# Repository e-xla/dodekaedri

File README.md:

# dodekaedri
dodekaedrin muotoinen radio ":D" /  dodecahedron shaped radio ":D"

------
This project aims to create truly affordable (<50€) 40m SSB QRP HAM radio kit.
Intention is to create such easy-approach kit that enables new (and old) HAMs to learn about radios, electronics and so on.

Some intended specs include:
* included SWR-meter
* ~5-10W of raw electromagnetic power
* graphical UI
* 2 mixer stages, one physical, one done with software

(Antenna not included)

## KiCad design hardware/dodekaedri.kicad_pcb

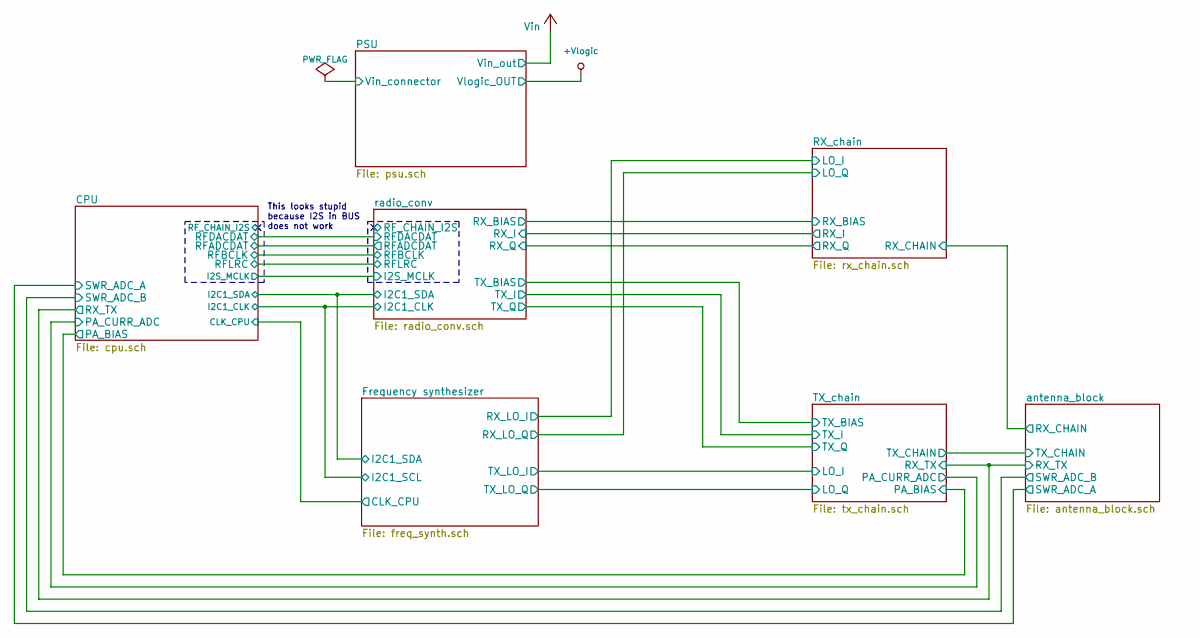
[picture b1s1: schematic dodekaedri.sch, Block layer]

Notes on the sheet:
This looks stupid because I2S in BUS does not work

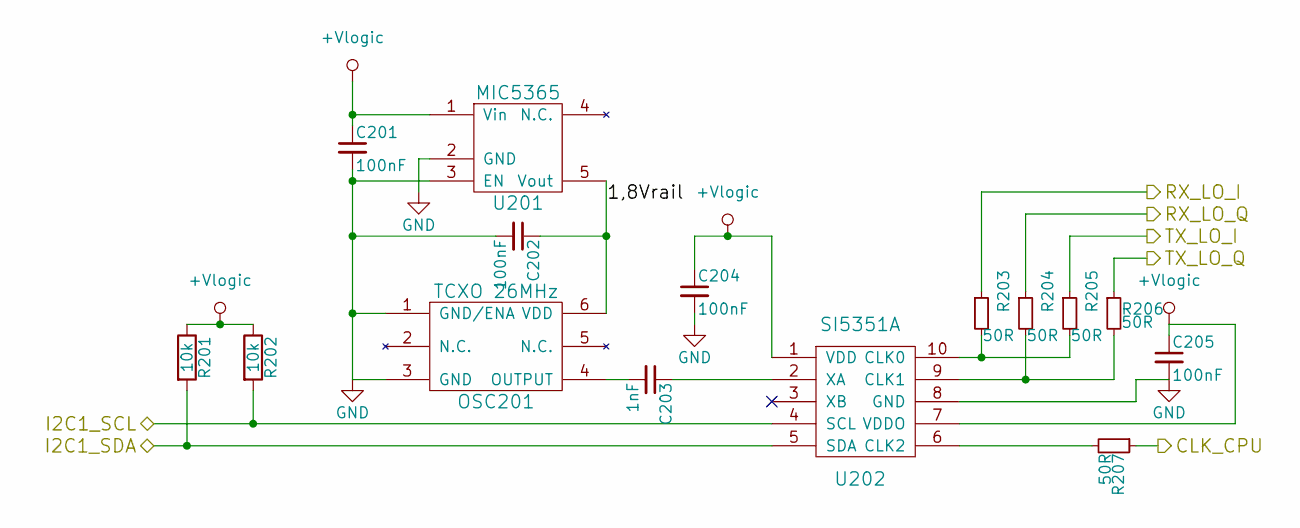
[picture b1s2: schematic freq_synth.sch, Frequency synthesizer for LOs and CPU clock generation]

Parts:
C201, C202, C204, C205: 100nF; C_0805
C203: 1nF; C_0805
OSC201: TCXO 26MHz
R201, R202: 10k; R_0805_HandSoldering
R203, R204, R205, R206, R207: 50R; R_0805_HandSoldering
U201: MIC5365
U202: SI5351A

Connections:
/CPU/CLK_CPU: R207.1; also elsewhere on the board
/CPU/I2C1_CLK: R202.2, U202.4 (SCL); also elsewhere on the board
/CPU/I2C1_SDA: R201.2, U202.5 (SDA); also elsewhere on the board
/Frequency synthesizer/1,8Vrail: C202.1, OSC201.6 (VDD), U201.5 (Vout)
/RX_chain/LO_I: R203.1; also elsewhere on the board
/RX_chain/LO_Q: R204.1; also elsewhere on the board
/TX_chain/LO_I: R205.1; also elsewhere on the board
/TX_chain/LO_Q: R206.1; also elsewhere on the board
GND: C201.2, C202.2, C204.2, C205.2, OSC201.1 (GND/ENA), OSC201.3 (GND), U201.2 (GND), U201.3 (EN), U202.8 (GND); also elsewhere on the board
unnamed: C203.1, U202.2 (XA)
unnamed: C203.2, OSC201.4 (OUTPUT)
unnamed: R203.2, R205.2, U202.10 (CLK0)
unnamed: R204.2, R206.2, U202.9 (CLK1)
unnamed: R207.2, U202.6 (CLK2)

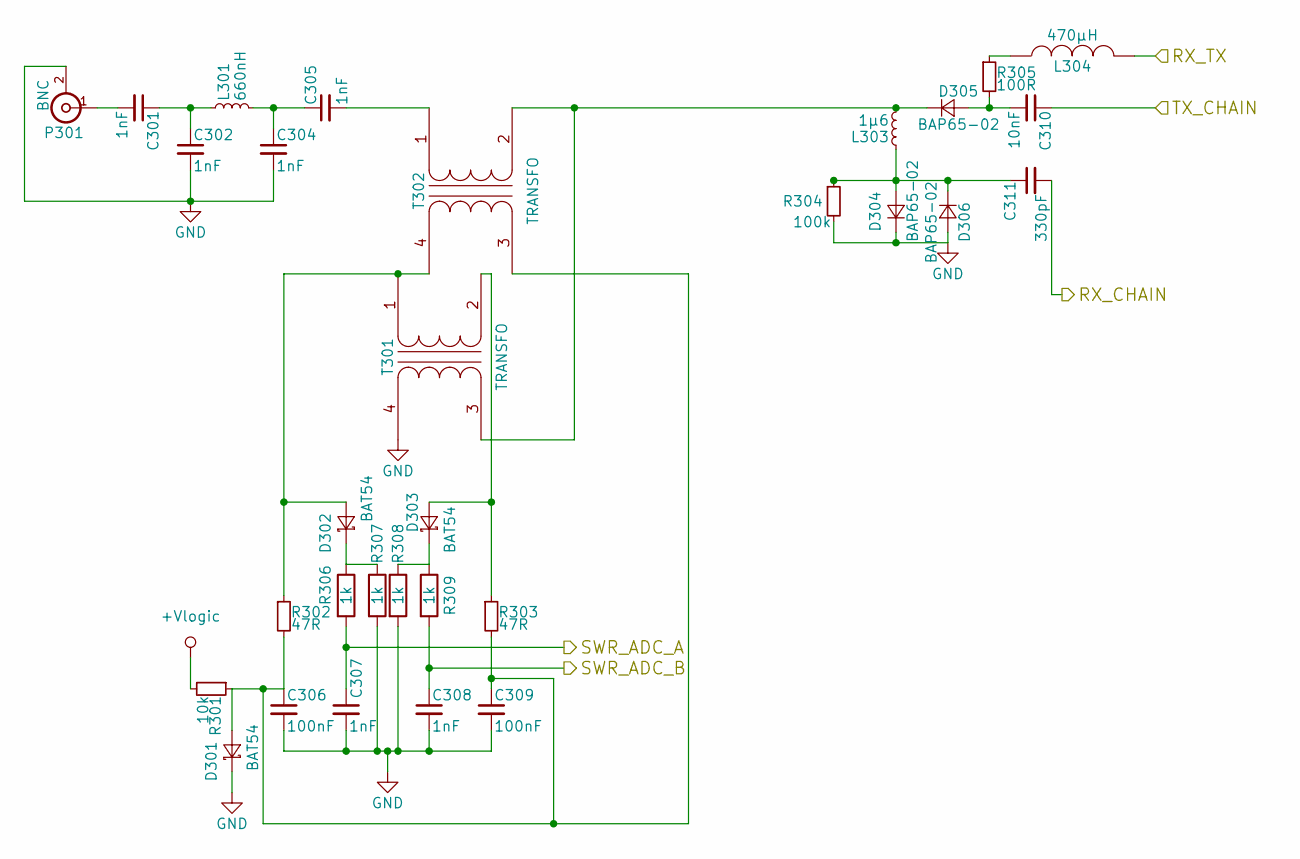
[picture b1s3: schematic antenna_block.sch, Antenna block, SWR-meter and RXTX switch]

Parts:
C301, C302, C304, C305, C307, C308: 1nF; C_0805_HandSoldering
C306, C309: 100nF; C_0805_HandSoldering
C310: 10nF; C_0805_HandSoldering
C311: 330pF; C_0805_HandSoldering
D301, D302, D303: BAT54; SOT-23_HS_2-1-3
D304, D305, D306: BAP65-02; SOD-523
L301: 660nH; Neosid_Air-Coil_SML_5turn_HDM0531A
L303: 1µ6; Neosid_Air-Coil_SML_5turn_HDM0531A
L304: 470µH; SMT_1007
P301: BNC; BNC_right_angle
R301: 10k; R_0805_HandSoldering
R302, R303: 47R; R_0805_HandSoldering
R304: 100k; R_0805_HandSoldering
R305: 100R; R_0805_HandSoldering
R306, R307, R308, R309: 1k; R_0805_HandSoldering
T301, T302: TRANSFO; TRANSF_pads

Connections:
/CPU/RX_TX: L304.2; also elsewhere on the board
/CPU/SWR_ADC_A: C307.1, R306.2; also elsewhere on the board
/CPU/SWR_ADC_B: C308.1, R309.2; also elsewhere on the board
/RX_chain/RX_CHAIN: C311.2; also elsewhere on the board
/TX_chain/TX_CHAIN: C310.1; also elsewhere on the board
GND: C302.2, C304.2, C306.2, C307.2, C308.2, C309.2, D301.1 (K), D304.1 (K), D306.2 (A), P301.2 (Ext), R304.2, R307.2, R308.2, T301.4 (SB); also elsewhere on the board
unnamed: C301.1, C302.1, L301.1
unnamed: C301.2, P301.1 (In)
unnamed: C304.1, C305.1, L301.2
unnamed: C305.2, T302.1 (AA)
unnamed: C306.1, C309.1, D301.2 (A), R301.1, R302.2, R303.2, T302.3 (SA)
unnamed: C310.2, D305.2 (A), R305.2
unnamed: C311.1, D304.2 (A), D306.1 (K), L303.1, R304.1
unnamed: D302.1 (K), R306.1, R307.1
unnamed: D302.2 (A), R302.1, T301.1 (AA), T302.4 (SB)
unnamed: D303.1 (K), R308.1, R309.1
unnamed: D303.2 (A), R303.1, T301.2 (AB)
unnamed: D305.1 (K), L303.2, T301.3 (SA), T302.2 (AB)
unnamed: L304.1, R305.1

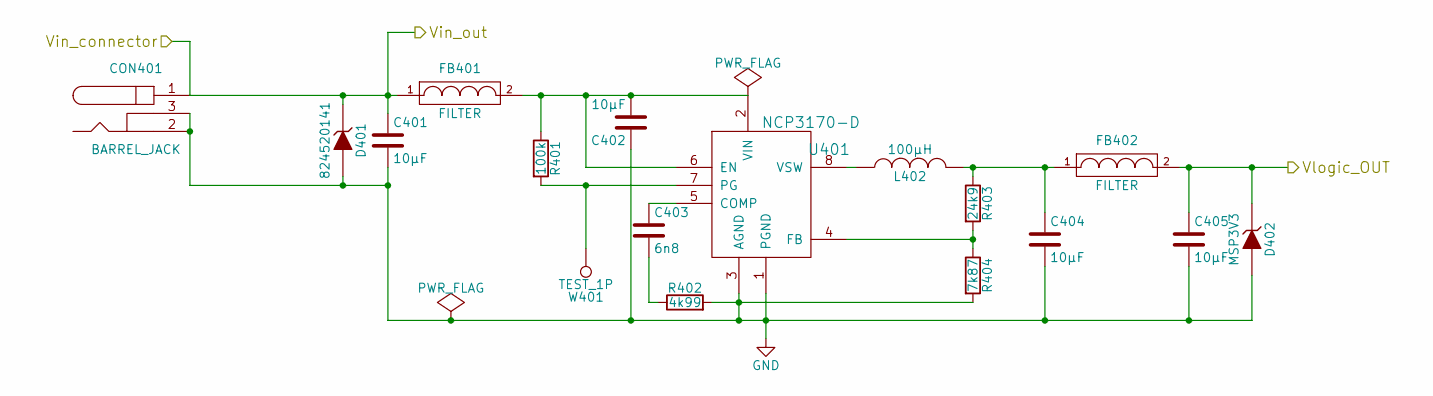
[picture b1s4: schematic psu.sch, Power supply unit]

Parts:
C401, C402, C404, C405: 10µF; C_0805_HandSoldering
C403: 6n8; C_0805_HandSoldering
CON401: BARREL_JACK
D401: 824520141; SMA_Handsoldering
D402: MSP3V3; Micro_SMP
FB401, FB402: FILTER; R_0805_HandSoldering
L402: 100µH; psu_ind
R401: 100k; R_0805_HandSoldering
R402: 4k99; R_0805_HandSoldering
R403: 24k9; R_0805_HandSoldering
R404: 7k87; R_0805_HandSoldering
U401: NCP3170-D; SOIC-8_3.9x4.9mm_Pitch1.27mm
W401: TEST_1P; Measurement_Point_Round-SMD-Pad_Big

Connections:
GND: C401.2, C402.1, C404.2, C405.2, CON401.2, CON401.3, D401.2 (A), D402.2 (A), R402.2, R404.2, U401.1 (PGND), U401.3 (AGND); also elsewhere on the board
unnamed: C402.2, FB401.2, R401.1, U401.2 (VIN), U401.6 (EN)
unnamed: C403.1, U401.5 (COMP)
unnamed: C403.2, R402.1
unnamed: C404.1, FB402.1, L402.2, R403.1
unnamed: L402.1, U401.8 (VSW)
unnamed: R401.2, U401.7 (PG), W401.1
unnamed: R403.2, R404.1, U401.4 (FB)
Vin_net: C401.1, CON401.1, D401.1 (K), FB401.1; also elsewhere on the board

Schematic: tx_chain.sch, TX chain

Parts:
C501: 220µF; CAP_6.3x5.8mm
C502, C505, C509: 100nF; C_0805_HandSoldering
C503, C512: 330pF; C_0805_HandSoldering
C504, C506, C507, C508, C510, C511: 10nF; C_0805_HandSoldering
C513: 1nF; C_0805_HandSoldering
D501: RED; LED_0805
FB501: FILTER; R_0805_HandSoldering
L501, L502: 1µH; Neosid_Air-Coil_SML_5turn_HDM0531A
L503: 800nH; Neosid_Air-Coil_SML_5turn_HDM0531A
Q501: BCP56; SOT-223
Q502: IRL510; TO-220_Neutral123_Vertical
R501, R502, R506, R507, R509, R510: 1k; R_0805_HandSoldering
R503: 50R; R_0805_HandSoldering
R504: 10R; R_0805_HandSoldering
R505: 0.1pF; R_0805_HandSoldering
R508: 0R1; R_0805_HandSoldering
R511: 100k; R_0805_HandSoldering
T501: TRANSFO2; transf_5_pin
U501, U502: 74LVC1G3157; SOT-23-6_Handsoldering

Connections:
/CPU/PA_BIAS: R510.1, R511.1; also elsewhere on the board
/CPU/PA_CURR_ADC: C511.1, R509.2; also elsewhere on the board
/CPU/RX_TX: R501.2; also elsewhere on the board
/TX_chain/LO_I: U501.6 (S); also elsewhere on the board
/TX_chain/LO_Q: U502.6 (S); also elsewhere on the board
/TX_chain/TX_BIAS: C501.1, C502.1, T501.4 (SB), T501.5 (SC); also elsewhere on the board
/TX_chain/TX_CHAIN: C513.1, L503.2; also elsewhere on the board
GND: C501.2, C502.2, C503.2, C505.2, C508.2, C509.2, C510.2, C511.2, C512.2, C513.2, D501.1, R504.2, R508.2, R511.2, T501.1 (AA), U501.2 (GND), U502.2 (GND); also elsewhere on the board
unnamed: C503.1, C504.1, L501.2
unnamed: C504.2, Q501.1 (B), R502.2
unnamed 68: C506.1, Q501.2 (C), R503.2; also elsewhere on the board
unnamed: C506.2, C507.1, R505.1
unnamed: C507.2, Q502.2 (G), R506.1
unnamed: C508.1, R506.2, R507.2
unnamed: C510.1, R507.1, R510.2
unnamed: C512.1, L502.2, L503.1, Q502.1 (D), R505.2
unnamed: D501.2, R501.1, R502.1
unnamed: L501.1, T501.2 (AB)
unnamed: Q501.3 (E), R504.1
unnamed: Q502.3 (S), R508.1, R509.1
unnamed 148: U501.4 (A); also elsewhere on the board
unnamed 149: U502.4 (A); also elsewhere on the board
unnamed: T501.3 (SA), U501.1 (B2), U502.1 (B2)
unnamed: T501.6 (SD), U501.3 (B1), U502.3 (B1)
Vin_net: FB501.1; also elsewhere on the board

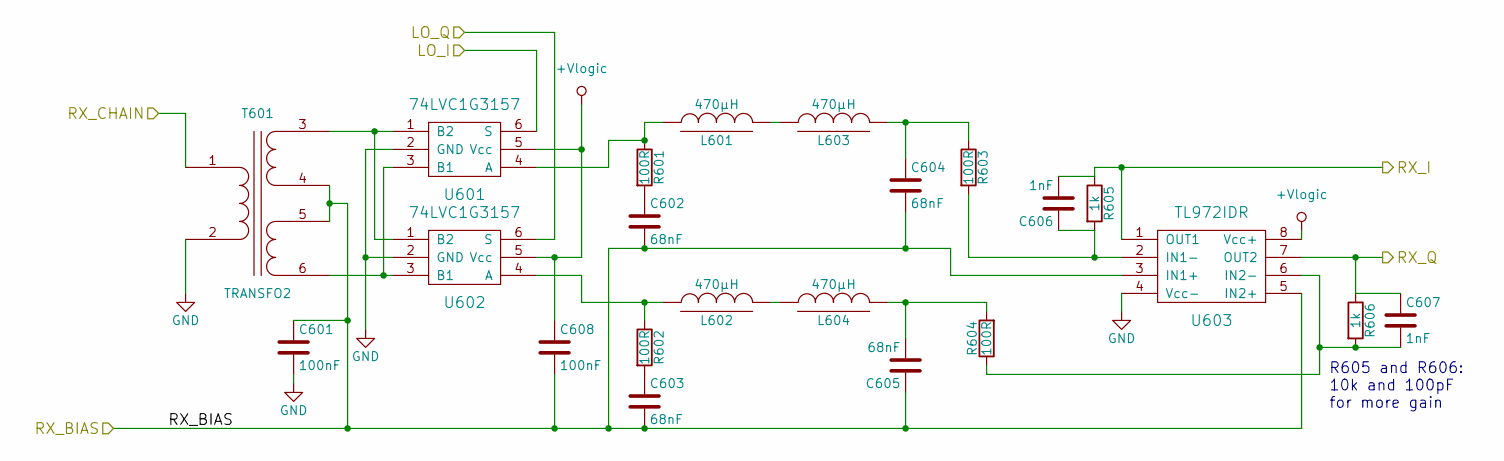
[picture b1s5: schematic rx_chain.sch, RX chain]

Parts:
C601, C608: 100nF; C_0805_HandSoldering
C602, C603, C604, C605: 68nF; C_0805_HandSoldering
C606, C607: 1nF; C_0805_HandSoldering
L601, L602, L603, L604: 470µH; SMT_1007
R601, R602, R603, R604: 100R; R_0805_HandSoldering
R605, R606: 1k; R_0805_HandSoldering
T601: TRANSFO2; transf_5_pin
U601, U602: 74LVC1G3157; SOT-23-6_Handsoldering
U603: TL972IDR; SOIC-8_3.9x4.9mm_Pitch1.27mm

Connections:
/RX_chain/LO_I: U601.6 (S); also elsewhere on the board
/RX_chain/LO_Q: U602.6 (S); also elsewhere on the board
/RX_chain/RX_BIAS: C601.1, C602.2, C603.2, C604.2, C605.1, C608.2, T601.4 (SB), T601.5 (SC), U603.3 (IN1+), U603.5 (IN2+); also elsewhere on the board
/RX_chain/RX_CHAIN: T601.1 (AA); also elsewhere on the board
/RX_chain/RX_I: C606.2, R605.1, U603.1 (OUT1); also elsewhere on the board
/RX_chain/RX_Q: C607.1, R606.1, U603.7 (OUT2); also elsewhere on the board
GND: C601.2, T601.2 (AB), U601.2 (GND), U602.2 (GND), U603.4 (Vcc-); also elsewhere on the board
unnamed: C602.1, R601.2
unnamed: C603.1, R602.2
unnamed: C604.1, L603.2, R603.1
unnamed: C605.2, L604.2, R604.2
unnamed: C606.1, R603.2, R605.2, U603.2 (IN1-)
unnamed: C607.2, R604.1, R606.2, U603.6 (IN2-)
unnamed: L601.1, R601.1, U601.4 (A)
unnamed: L601.2, L603.1
unnamed: L602.1, R602.1, U602.4 (A)
unnamed: L602.2, L604.1
unnamed: T601.3 (SA), U601.1 (B2), U602.1 (B2)
unnamed: T601.6 (SD), U601.3 (B1), U602.3 (B1)

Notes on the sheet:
R605 and R606: 10k and 100pF for more gain

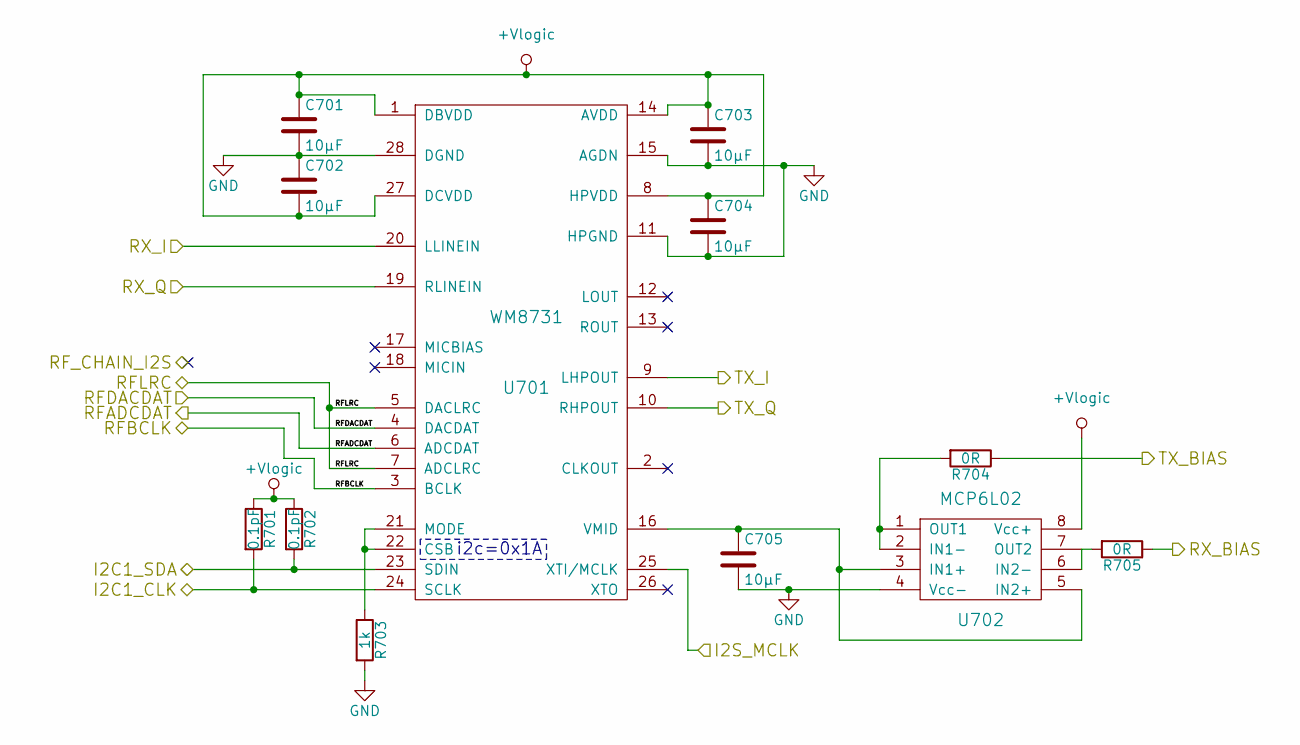
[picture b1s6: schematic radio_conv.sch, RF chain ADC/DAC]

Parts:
C701, C702, C703, C704, C705: 10µF; C_0805_HandSoldering
R701, R702: 0.1pF; R_0805_HandSoldering
R703: 1k; R_0805_HandSoldering
R704, R705: 0R; R_0805_HandSoldering
U701: WM8731; SSOP-28_5.3x10.2mm_Pitch0.65mm
U702: MCP6L02; SOIC-8_3.9x4.9mm_Pitch1.27mm

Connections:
/CPU/I2C1_CLK: R701.2, U701.24 (SCLK); also elsewhere on the board
/CPU/I2C1_SDA: R702.2, U701.23 (SDIN); also elsewhere on the board
/CPU/I2S_MCLK: U701.25 (XTI/MCLK); also elsewhere on the board
/CPU/RFADCDAT: U701.6 (ADCDAT); also elsewhere on the board
/CPU/RFBCLK: U701.3 (BCLK); also elsewhere on the board
/CPU/RFDACDAT: U701.4 (DACDAT); also elsewhere on the board
/CPU/RFLRC: U701.5 (DACLRC), U701.7 (ADCLRC); also elsewhere on the board
/RX_chain/RX_BIAS: R705.1; also elsewhere on the board
/RX_chain/RX_I: U701.20 (LLINEIN); also elsewhere on the board
/RX_chain/RX_Q: U701.19 (RLINEIN); also elsewhere on the board
/TX_chain/TX_BIAS: R704.1; also elsewhere on the board
/TX_chain/TX_I: U701.9 (LHPOUT); also elsewhere on the board
/TX_chain/TX_Q: U701.10 (RHPOUT); also elsewhere on the board
GND: C701.2, C702.1, C703.2, C704.2, C705.2, R703.2, U701.11 (HPGND), U701.15 (AGDN), U701.28 (DGND), U702.4 (Vcc-); also elsewhere on the board
unnamed: C705.1, U701.16 (VMID), U702.3 (IN1+), U702.5 (IN2+)
unnamed: R703.1, U701.21 (MODE), U701.22 (CSB)
unnamed: R704.2, U702.1 (OUT1), U702.2 (IN1-)
unnamed: R705.2, U702.6 (IN2-), U702.7 (OUT2)

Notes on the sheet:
i2c=0x1A

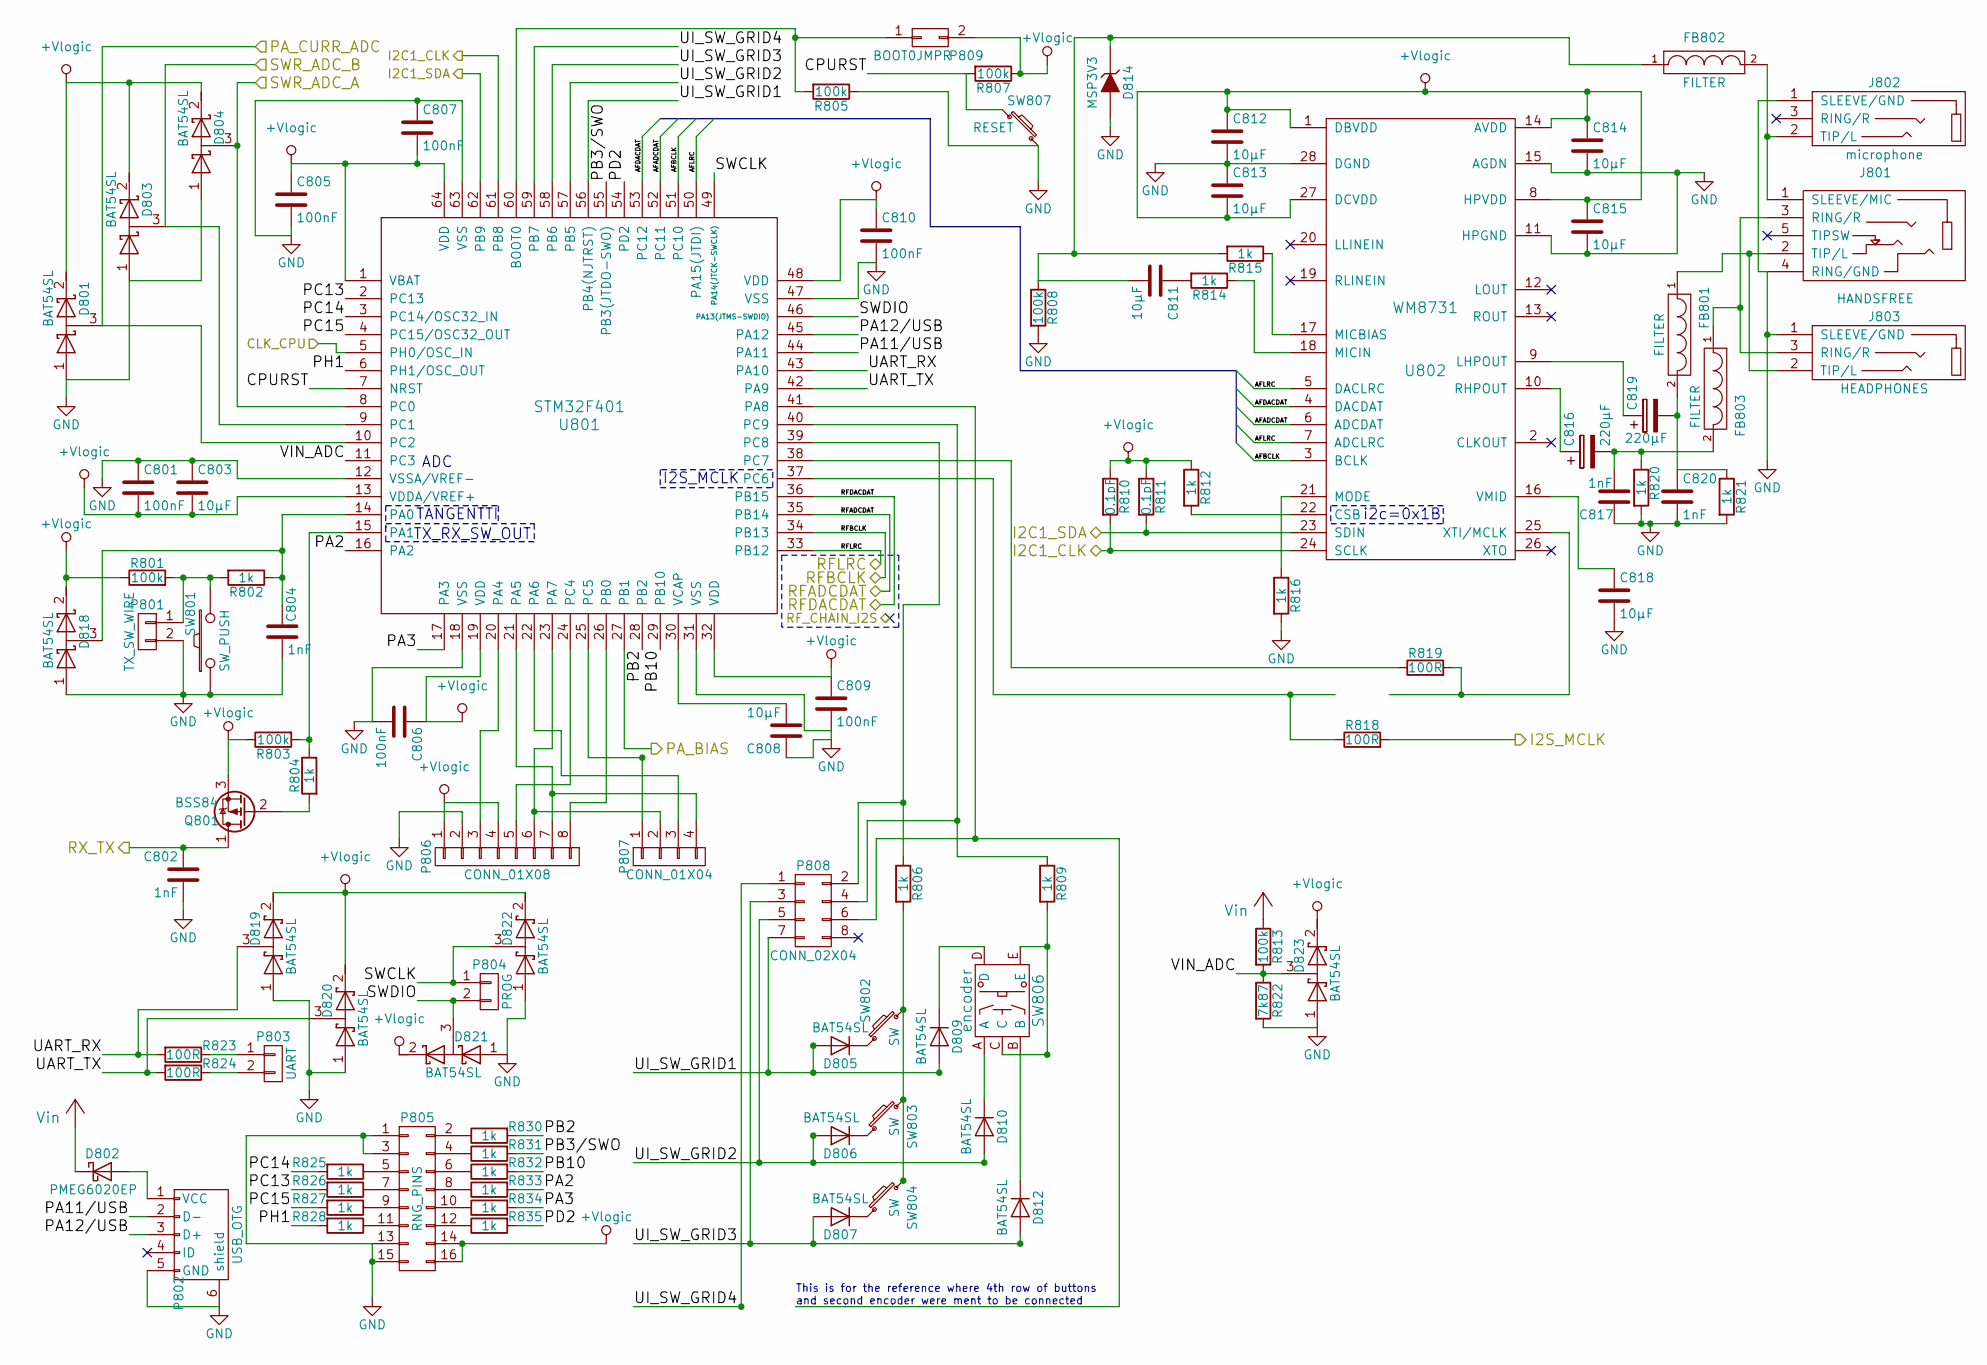
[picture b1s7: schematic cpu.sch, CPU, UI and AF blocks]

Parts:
C801, C805, C806, C807, C809, C810: 100nF; C_0805_HandSoldering
C802, C804, C817, C820: 1nF; C_0805_HandSoldering
C803, C808, C811, C812, C813, C814, C815, C818: 10µF; C_0805_HandSoldering
C816, C819: 220µF; CAP_6.3x5.8mm
D801, D803, D804, D818, D819, D820, D821, D822, D823: BAT54SL; SOT-23_Handsoldering
D802: PMEG6020EP; D_0805
D805, D806, D807, D809, D810, D812: BAT54SL; SOT-23_HS_2-1-3
D814: MSP3V3; Micro_SMP
FB801, FB802, FB803: FILTER; R_0805_HandSoldering
J801: HANDSFREE; TRRS_jack
J802: microphone
J803: HEADPHONES
P801: TX_SW_WIRE; AK300-2
P802: USB_OTG; USB_Micro-B
P803: UART; Pin_Header_Straight_1x02
P804: PROG; Pin_Header_Straight_1x02
P805: RNG_PINS; Pin_Header_Straight_2x08
P806: CONN_01X08; Pin_Header_Straight_1x08
P807: CONN_01X04; Pin_Header_Straight_1x04
P808: CONN_02X04; Pin_Header_Straight_2x04
P809: BOOT0JMPR; Pin_Header_Straight_1x02
Q801: BSS84; SOT-23_Handsoldering
R801, R803, R805, R807, R808, R813: 100k; R_0805_HandSoldering
R802, R804, R806, R809, R812, R814, R815, R816, R820, R821, R825, R826, R827, R828, R830, R831, R832, R833, R834, R835: 1k; R_0805_HandSoldering
R810, R811: 0.1pF; R_0805_HandSoldering
R818, R819, R823, R824: 100R; R_0805_HandSoldering
R822: 7k87; R_0805_HandSoldering
SW801: SW_PUSH; SW_SPST_B3SL-1002P
SW802, SW803, SW804: SW; SW_SPST_B3SL-1002P
SW806: encoder
SW807: RESET; SW_SPST_B3SL-1002P
U801: STM32F401; LQFP-64_10x10mm_Pitch0.5mm
U802: WM8731; SSOP-28_5.3x10.2mm_Pitch0.65mm

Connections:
/CPU/AFADCDAT: U801.52 (PC11), U802.6 (ADCDAT)
/CPU/AFBCLK: U801.51 (PC10), U802.3 (BCLK)
/CPU/AFDACDAT: U801.53 (PC12), U802.4 (DACDAT)
/CPU/AFLRC: U801.50 (PA15(JTDI)), U802.5 (DACLRC), U802.7 (ADCLRC)
/CPU/CLK_CPU: U801.5 (PH0/OSC_IN); also elsewhere on the board
/CPU/CPURST: R807.2, SW807.1, U801.7 (NRST)
/CPU/I2C1_CLK: R810.2, U801.61 (PB8), U802.24 (SCLK); also elsewhere on the board
/CPU/I2C1_SDA: R811.2, U801.62 (PB9), U802.23 (SDIN); also elsewhere on the board
/CPU/I2S_MCLK: R818.2; also elsewhere on the board
/CPU/PA2: R833.2, U801.16 (PA2)
/CPU/PA3: R834.2, U801.17 (PA3)
/CPU/PA11/USB: P802.2 (D-), U801.44 (PA11)
/CPU/PA12/USB: P802.3 (D+), U801.45 (PA12)
/CPU/PA_BIAS: U801.27 (PB1); also elsewhere on the board
/CPU/PA_CURR_ADC: D801.3 (common), U801.10 (PC2); also elsewhere on the board
/CPU/PB2: R830.2, U801.28 (PB2)
/CPU/PB3/SWO: R831.2, U801.55 (PB3(JTDO-SWO))
/CPU/PB10: R832.2, U801.29 (PB10)
/CPU/PC13: R826.2, U801.2 (PC13)
/CPU/PC14: R825.2, U801.3 (PC14/OSC32_IN)
/CPU/PC15: R827.2, U801.4 (PC15/OSC32_OUT)
/CPU/PD2: R835.2, U801.54 (PD2)
/CPU/PH1: R828.2, U801.6 (PH1/OSC_OUT)
/CPU/RFADCDAT: U801.35 (PB14); also elsewhere on the board
/CPU/RFBCLK: U801.34 (PB13); also elsewhere on the board
/CPU/RFDACDAT: U801.36 (PB15); also elsewhere on the board
/CPU/RFLRC: U801.33 (PB12); also elsewhere on the board
/CPU/RX_TX: C802.1, Q801.1 (D); also elsewhere on the board
/CPU/SWCLK: D822.3 (common), P804.1, U801.49 (PA14(JTCK-SWCLK))
/CPU/SWDIO: D821.3 (common), P804.2, U801.46 (PA13(JTMS-SWDIO))
/CPU/SWR_ADC_A: D804.3 (common), U801.8 (PC0); also elsewhere on the board
/CPU/SWR_ADC_B: D803.3 (common), U801.9 (PC1); also elsewhere on the board
/CPU/UART_RX: D819.3 (common), R823.2, U801.43 (PA10)
/CPU/UART_TX: D820.3 (common), R824.2, U801.42 (PA9)
/CPU/UI_SW_GRID1: D805.2 (A), D809.2 (A), P808.7, U801.56 (PB4(NJTRST))
/CPU/UI_SW_GRID2: D806.2 (A), D810.2 (A), P808.5, U801.57 (PB5)
/CPU/UI_SW_GRID3: D807.2 (A), D812.2 (A), P808.3, U801.58 (PB6)
/CPU/UI_SW_GRID4: P808.1, U801.59 (PB7)
/CPU/VIN_ADC: D823.3 (common), R813.2, R822.1, U801.11 (PC3)
GND: C801.1, C802.2, C803.1, C804.2, C805.2, C806.2, C807.1, C808.1, C809.2, C810.2, C812.2, C813.1, C814.2, C815.2, C817.2, C818.2, C820.2, D801.1 (A), D803.1 (A), D804.1 (A), D814.2 (A), D818.1 (A), D819.1 (A), D820.1 (A), D821.1 (A), D822.1 (A), D823.1 (A), J801.4 (RING/GND), J802.1 (SLEEVE/GND), J803.1 (SLEEVE/GND), P801.2, P802.5 (GND), P802.6 (shield), P805.1, P805.3, P805.13, P805.15, P806.2, R805.1, R808.2, R816.2, R820.2, R821.2, R822.2, SW801.1, SW807.2, U801.12 (VSSA/VREF-), U801.18 (VSS), U801.31 (VSS), U801.47 (VSS), U801.63 (VSS), U802.11 (HPGND), U802.15 (AGDN), U802.28 (DGND); also elsewhere on the board
unnamed: C804.1, D818.3 (common), R802.1, U801.14 (PA0)
unnamed: C808.2, U801.30 (VCAP)
unnamed: C811.1, R814.2
unnamed: C811.2, D814.1 (K), FB802.1, R808.1, R815.2
unnamed: C816.1, U802.10 (RHPOUT)
unnamed: C816.2, C817.1, FB803.2, R820.1
unnamed: C818.1, U802.16 (VMID)
unnamed: C819.1, U802.9 (LHPOUT)
unnamed: C819.2, C820.1, FB801.2, R821.1
unnamed: D802.2 (A), P802.1 (VCC)
unnamed: D805.1 (K), SW802.1
unnamed: D806.1 (K), SW803.1
unnamed: D807.1 (K), SW804.1
unnamed: D809.1 (K), SW806.D
unnamed: D810.1 (K), SW806.A
unnamed: D812.1 (K), SW806.B
unnamed: FB801.1, J801.2 (TIP/L), J803.2 (TIP/L)
unnamed: FB802.2, J801.1 (SLEEVE/MIC), J802.2 (TIP/L)
unnamed: FB803.1, J801.3 (RING/R), J803.3 (RING/R)
unnamed: P801.1, R801.2, R802.2, SW801.2
unnamed: P803.1, R823.1
unnamed: P803.2, R824.1
unnamed: P805.2, R830.1
unnamed: P805.4, R831.1
unnamed: P805.5, R825.1
unnamed: P805.6, R832.1
unnamed: P805.7, R826.1
unnamed: P805.8, R833.1
unnamed: P805.9, R827.1
unnamed: P805.10, R834.1
unnamed: P805.11, R828.1
unnamed: P805.12, R835.1
unnamed: P806.3, U801.20 (PA4)
unnamed: P806.5, U801.24 (PC4)
unnamed: P806.6, P807.2, U801.23 (PA7)
unnamed: P806.7, P807.4, U801.21 (PA5)
unnamed: P806.8, U801.26 (PB0)
unnamed: P807.1, U801.25 (PC5)
unnamed: P807.3, U801.22 (PA6)
unnamed: P808.2, R806.1, U801.39 (PC8)
unnamed: P808.4, R809.1, U801.40 (PC9)
unnamed: P808.6, U801.41 (PA8)
unnamed: P809.1, R805.2, U801.60 (BOOT0)
unnamed: Q801.2 (G), R804.2
unnamed: R803.2, R804.1, U801.15 (PA1)
unnamed: R806.2, SW802.2, SW803.2, SW804.2
unnamed: R809.2, SW806.C, SW806.E
unnamed: R812.2, U802.22 (CSB)
unnamed: R814.1, U802.18 (MICIN)
unnamed: R815.1, U802.17 (MICBIAS)
unnamed: R816.1, U802.21 (MODE)
unnamed: R818.1, U801.37 (PC6)
unnamed: R819.1, U801.38 (PC7)
unnamed: R819.2, U802.25 (XTI/MCLK)
Vin_net: D802.1 (K), R813.1; also elsewhere on the board

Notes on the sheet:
i2c=0x1B
I2S_MCLK
ADC
TANGENTTI
TX_RX_SW_OUT
This is for the reference where 4th row of buttons and second encoder were ment to be connected

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
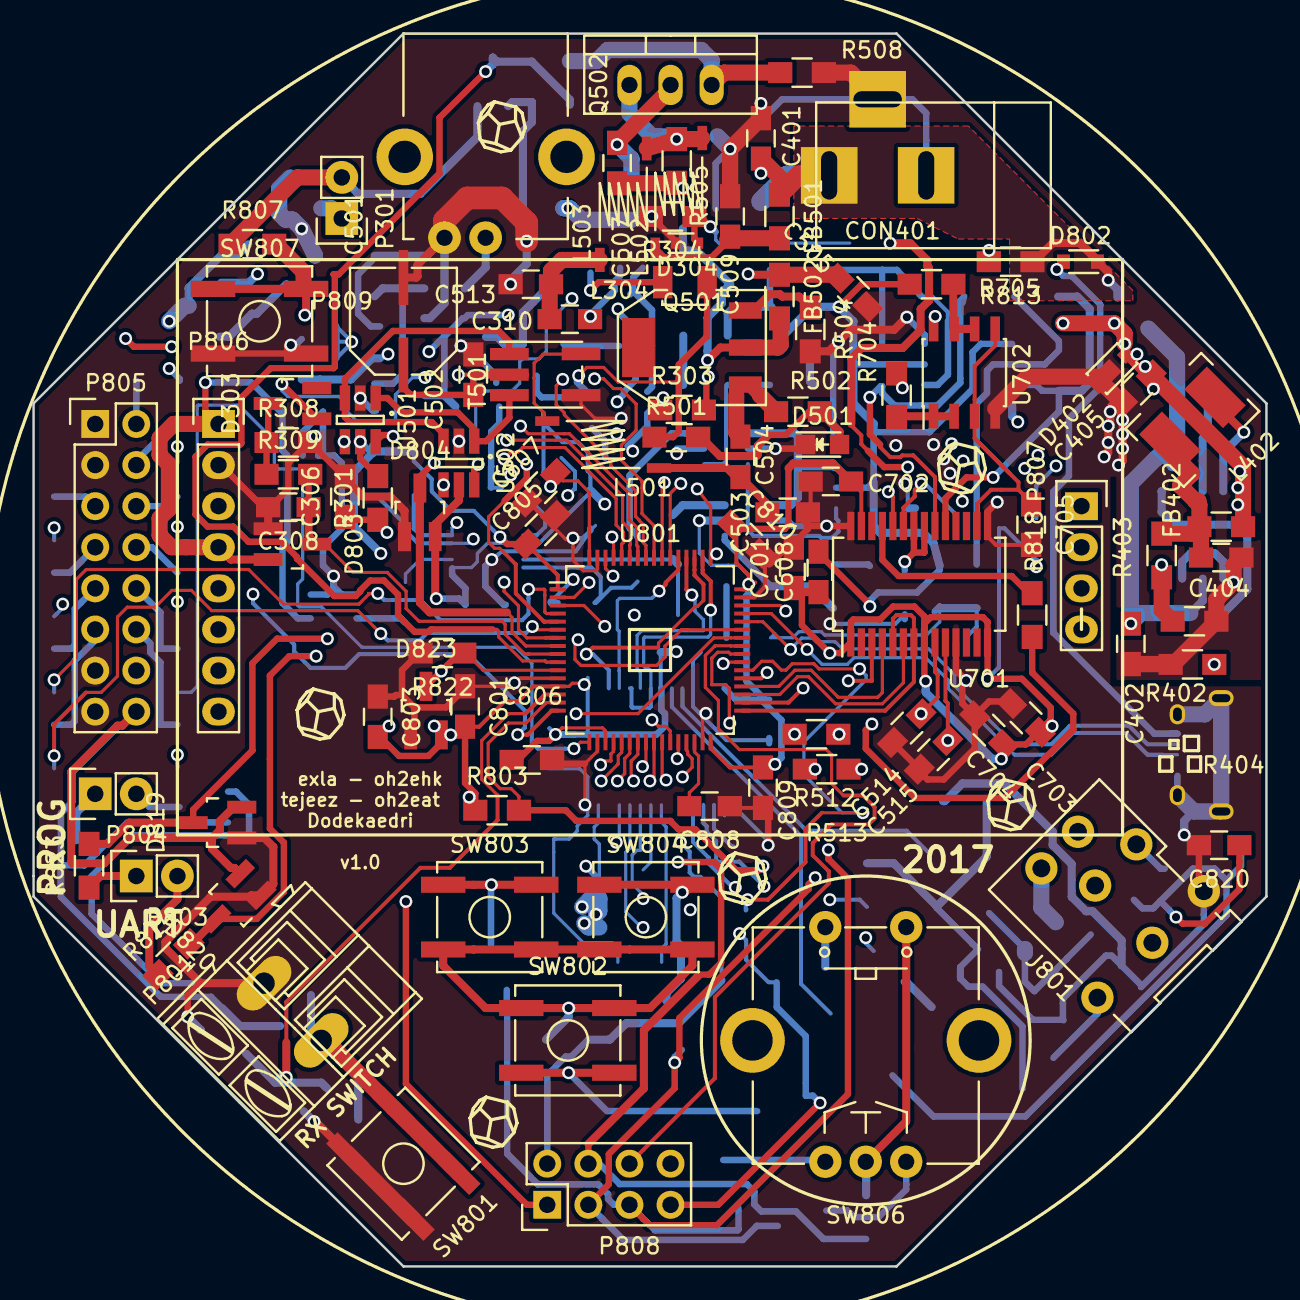
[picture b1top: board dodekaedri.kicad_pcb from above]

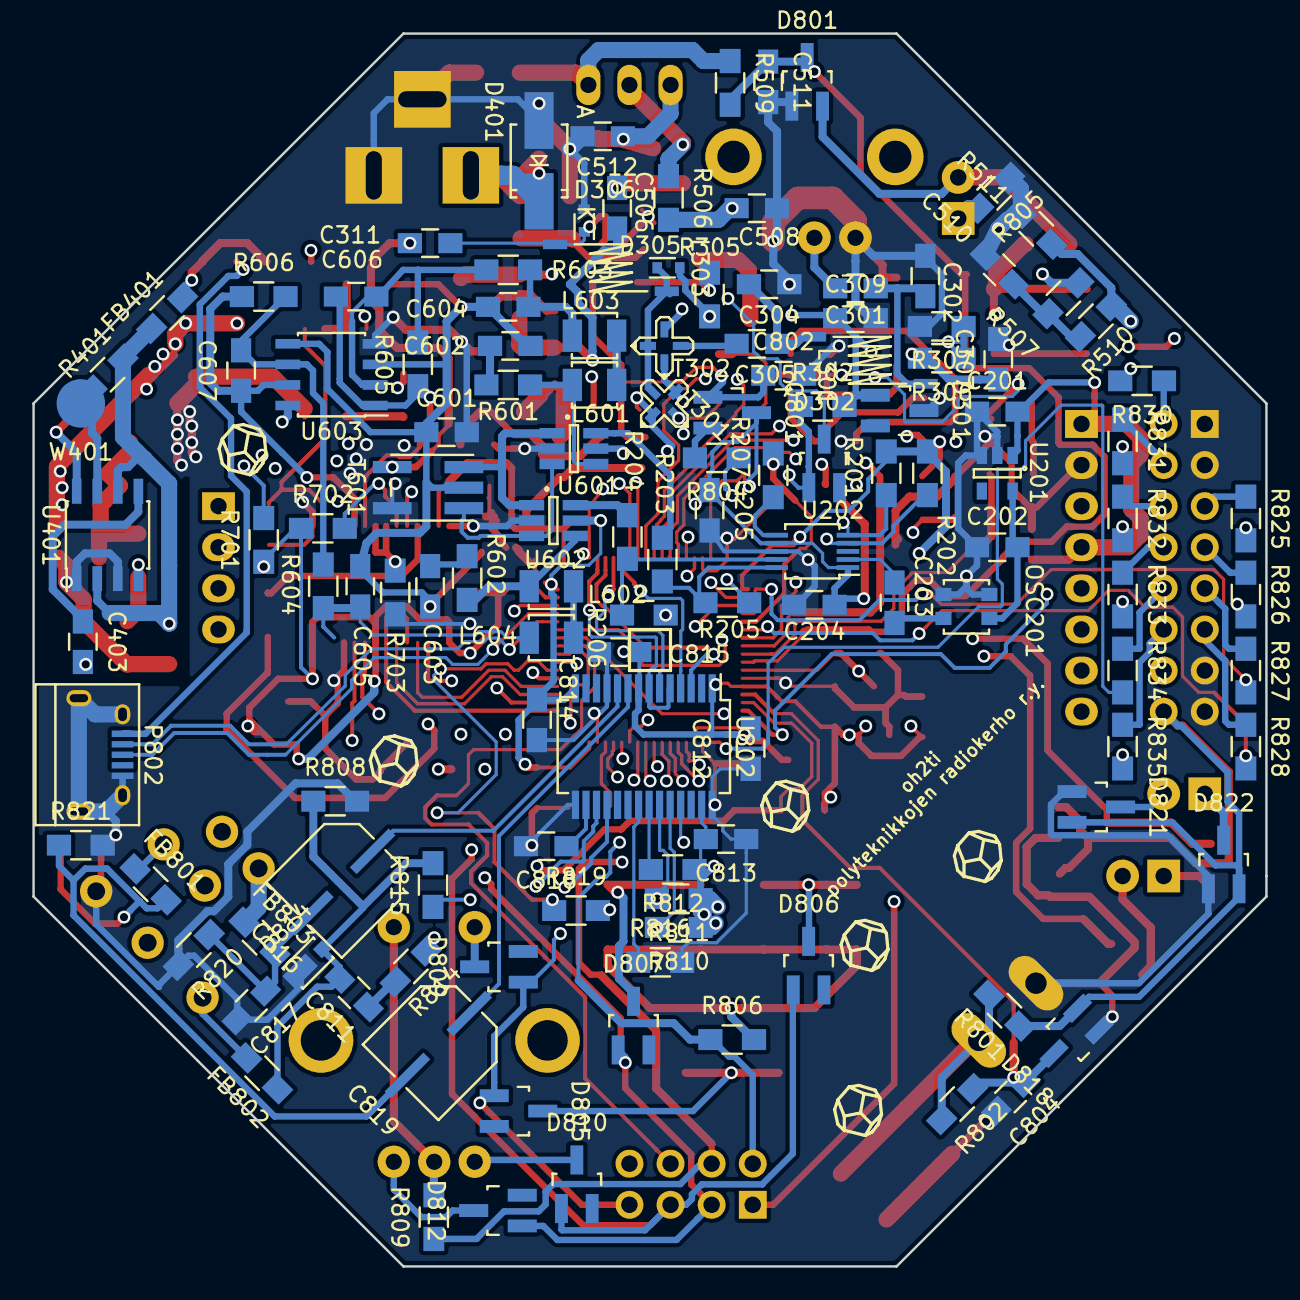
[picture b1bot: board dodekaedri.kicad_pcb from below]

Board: 4 copper layers, 76.2 x 76.2 mm, 227 parts (128 on the bottom side), 167 nets.

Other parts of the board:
C514, C515: 1nF; C_0805_HandSoldering
FB502: FILTER; R_0805_HandSoldering
R512, R513: 100R; R_0805_HandSoldering

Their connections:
/TX_chain/TX_I: C514.1, R512.2; also elsewhere on the board
/TX_chain/TX_Q: C515.1, R513.2; also elsewhere on the board
GND: C514.2, C515.2; also elsewhere on the board
unnamed 68: FB502.2; also elsewhere on the board
unnamed 148: R512.1; also elsewhere on the board
unnamed 149: R513.1; also elsewhere on the board

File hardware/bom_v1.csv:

Value, Count, single price, total, References
"0.1pF",5,0,0,"R505" "R701" "R702" "R810" "R811" 
"0R",2,0,0,"R704" "R705" 
"0R1",1,0,0,"R508" 
"100R",16,0,0,"R207" "R205" "R206" "R204" "R203" "R305" "R512" "R513" "R601" "R602" "R603" "R604" "R818" "R819" "R823" "R824" 
"100k",9,0,0,"R304" "R401" "R511" "R808" "R803" "R801" "R805" "R807" "R813" 
"100nF",17,0,0,"C202" "C201" "C205" "C204" "C309" "C306" "C502" "C505" "C509" "C601" "C608" "C805" "C807" "C801" "C810" "C806" "C809" 
"100µH",1,0,0,"L402" 
"10R",1,0,0,"R504" 
"10nF",7,0,0,"C310" "C504" "C506" "C507" "C511" "C508" "C510" 
"10µF",17,0,0,"C402" "C404" "C401" "C405" "C701" "C702" "C703" "C704" "C705" "C803" "C812" "C813" "C814" "C815" "C818" "C808" "C811" 
"1k",35,0,0,"R201" "R202" "R307" "R306" "R308" "R309" "R506" "R502" "R509" "R507" "R510" "R501" "R605" "R606" "R703" "R812" "R816" "R815" "R814" "R802" "R804" "R806" "R809" "R820" "R821" "R830" "R831" "R832" "R833" "R834" "R835" "R825" "R826" "R827" "R828" 
"1nF",16,0,0,"C203" "C301" "C302" "C304" "C305" "C307" "C308" "C513" "C514" "C515" "C606" "C607" "C817" "C820" "C802" "C804" 
"1µ6",1,0,0,"L303" 
"1µH",2,0,0,"L501" "L502" 
"220µF",3,0,0,"C501" "C819" "C816" 
"24k9",1,0,0,"R403" 
"330pF",3,0,0,"C311" "C503" "C512" 
"470µH",5,0,0,"L304" "L601" "L603" "L602" "L604" 
"47R",2,0,0,"R302" "R303" 
"4k99",1,0,0,"R402" 
"660nH",1,0,0,"L301" 
"68nF",4,0,0,"C602" "C603" "C605" "C604" 
"6n8",1,0,0,"C403" 
"74LVC1G3157",4,0,0,"U501" "U502" "U601" "U602" 
"7k87",3,0,0,"R301" "R404" "R822" 
"800nH",1,0,0,"L503" 
"824520141",1,0,0,"D401" 
"BA891",3,0,0,"D304" "D305" "D306" 
"BARREL_JACK",1,0,0,"CON401" 
"BAT54SL",18,0,0,"D301" "D302" "D303" "D801" "D803" "D804" "D805" "D806" "D807" "D809" "D812" "D810" "D823" "D819" "D820" "D822" "D821" "D818" 
"BCP56",1,0,0,"Q501" 
"BNC",1,0,0,"P301" 
"BOOT0JMPR",1,0,0,"P809" 
"BSS84",1,0,0,"Q801" 
"CONN_01X04",1,0,0,"P807" 
"CONN_01X08",1,0,0,"P806" 
"CONN_02X04",1,0,0,"P808" 
"FILTER",7,0,0,"FB401" "FB402" "FB501" "FB502" "FB802" "FB803" "FB801" 
"HANDSFREE",1,0,0,"J801" 
"HEADPHONES",1,0,0,"J803" 
"IRL510",1,0,0,"Q502" 
"MCP6L02",1,0,0,"U702" 
"MIC5365",1,0,0,"U201" 
"MSP3V3",2,0,0,"D402" "D814" 
"NCP3170-D",1,0,0,"U401" 
"PMEG6020EP",1,0,0,"D802" 
"PROG",1,0,0,"P804" 
"RED",1,0,0,"D501" 
"RESET",1,0,0,"SW807" 
"RNG_PINS",1,0,0,"P805" 
"SI5351A",1,0,0,"U202" 
"STM32F401",1,0,0,"U801" 
"SW",3,0,0,"SW802" "SW803" "SW804" 
"SW_PUSH",1,0,0,"SW801" 
"TCXO 26MHz",1,0,0,"OSC201" 
"TEST_1P",1,0,0,"W401" 
"TL972IDR",1,0,0,"U603" 
"TRANSFO",2,0,0,"T302" "T301" 
"TRANSFO2",2,0,0,"T501" "T601" 
"TX_SW_WIRE",1,0,0,"P801" 
"UART",1,0,0,"P803" 
"USB_OTG",1,0,0,"P802" 
"WM8731",2,0,0,"U701" "U802" 
"encoder",1,0,0,"SW806" 
"microphone",1,0,0,"J802"
